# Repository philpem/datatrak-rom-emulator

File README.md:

EPROM Emulator for Datatrak Locator
===================================

This is a plug-in card which replaces the Datatrak "B7415" plug-in ROM card
used with the Locator Mk. II. Its purpose is to allow easier development of
alternative firmware for the Datatrak Locator II, and reverse engineering
of the hardware.

It consists of a 256Kx16 SRAM (512KiB) which can be loaded via an FTDI
FT240X USB serial FIFO and a Xilinx XC95144XL CPLD. The CPLD is programmed
using a JTAG cable.

Mod wires
---------
Rev 'A' boards require a 'mod wire' to be fitted between pin 135 of IC2
(the Xilinx CPLD) and either pin 10 of the SRAM or pin 37 of U3 (the
uppermost voltage level translator).

This wire carries D8 (level translated) from the level translator and SRAM
to the CPLD. Failure to install this wire will prevent D8 from being loaded
by the CPLD.

Known limitations
-----------------

  * The SRAM is powered from the target. Disconnecting target power will
    cause the loss of the data in the emulated EPROM.

    * It might be a good idea to break the power supply to the SRAM and
      feed it via two Schottky diodes: one from +3V3 and one from the FTDI's
      3V output.
      This way, the RAM will be maintained as long as either the USB or
      target is powered.

CPLD configuration
------------------
The CPLD must be programmed before the ROM emulator can be used.

  1. Apply 5V power through the DIN41612 target connector.
  2. 5V power is applied to pins A1 and B1 of the connector, while ground
     is applied to pins A16 and B16.
  3. 3.3V DC should be present on the output of voltage regulator IC1, and
     on JTAG connector X3.
  4. Connect a Xilinx Platform Cable USB (if using iMPACT) or Altera USB
     JTAG cable (if using OpenOCD) to JTAG connector X3.
  5. Use Xilinx iMPACT, OpenOCD or similar to program the CPLD.
    - It's probably easiest to use iMPACT.
  6. Disconnect the JTAG cable, 5V power, etc.
  7. Plug the pod into the Locator and load it.

FT240X configuration
--------------------
The FT240X needs to be programmed with FT-PROG.

  * Program CBUS5 to output the 24MHz clock.
    * This is used by the CPLD as a clock for the state machine.

Exfiltration mode
-----------------
This mode allows the target to access a specially-designated port to use as
a return-channel to the emulation control PC. Essentially, this is like a
secondary, lightweight, "printf".

When an access is made in a specially designated range (address lines
A8..A17 match a preset value), the value of address lines A0 through A7 is
latched, then sent to the FT240X as "write data".

This data may be read by the host PC at its convenience.

It would be nice to add an "infiltration mode" to send data from the PC to
the Locator, but "printf" was a higher priority.

Load protocol
-------------

The data in the FTDI buffer consists of Commands and Data. These are the
Commands which the state machine currently recognises:

  * 0b0000\_0000: NOP
    * Does nothing.
    * Used to reset the state machine to a known state.

  * 0b0000\_0001: Reset Memory Address Counter
    * Resets the memory address to zero

  * 0b0001\_Xemm: Set Mode
    * X: don't care
    * e: Exfiltration mode on/off
      * 0: Off
      * 1: On
    * mm: Mode
      * 00: Run
      * 01: Load

  * 0b0010\_nnnn: Write _nnnn_ words
    * nnnn: Number of words to write
    * Followed by _nnnn_ words of ROM data

  * 0b0100\_xxEE: Set Exfiltration Address
    * EE: Top two bits of exfiltration address (b17..b16)
    * Followed by a byte which contains bits 15..8 of the exfiltration
      address
    * Bits 7..0 are the exfiltration data itself

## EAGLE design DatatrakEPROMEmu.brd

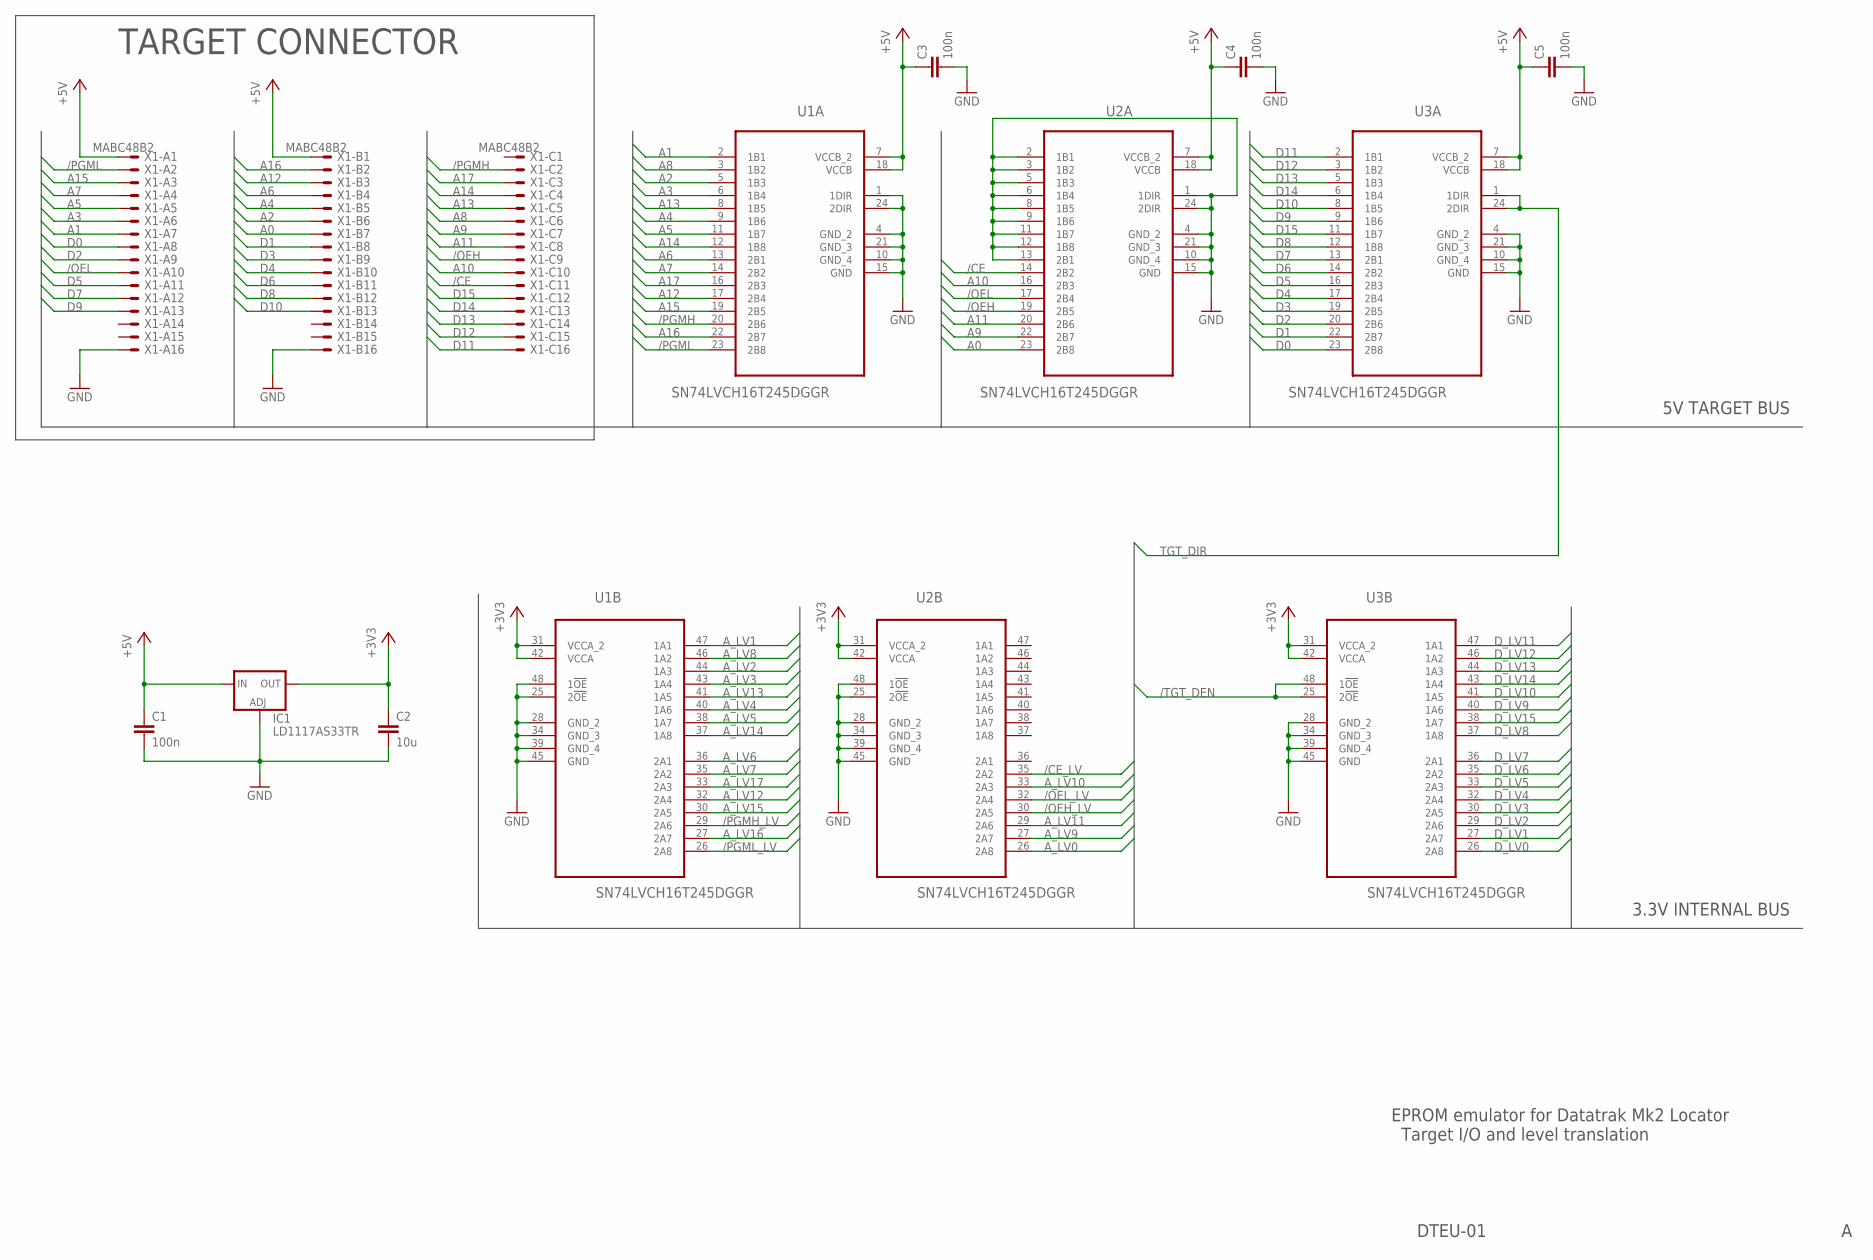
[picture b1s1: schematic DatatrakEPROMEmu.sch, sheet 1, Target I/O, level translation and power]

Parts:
C1, C3, C4, C5: 100n; C0805
C2: 10u; C0805
IC1: LD1117AS33TR; SOT223
U1, U2, U3: SN74LVCH16T245DGGR; SOP50P810X120-48N
X1: MABC48B2

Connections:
+3V3: C2.1, IC1.4 (OUT), U1.31 (VCCA_2), U1.42 (VCCA), U2.31 (VCCA_2), U2.42 (VCCA), U3.31 (VCCA_2), U3.42 (VCCA); also elsewhere on the board
+5V: C1.1, C3.1, C4.1, C5.1, IC1.3 (IN), U1.7 (VCCB_2), U1.18 (VCCB), U2.7 (VCCB_2), U2.18 (VCCB), U3.7 (VCCB_2), U3.18 (VCCB), X1.A1, X1.B1
/CE: U2.14 (2B2), X1.C11
/CE_LV: U2.35 (2A2); also elsewhere on the board
/OEH: U2.19 (2B5), X1.C9
/OEH_LV: U2.30 (2A5); also elsewhere on the board
/OEL: U2.17 (2B4), X1.A10
/OEL_LV: U2.32 (2A4); also elsewhere on the board
/PGMH: U1.20 (2B6), X1.C2
/PGMH_LV: U1.29 (2A6); also elsewhere on the board
/PGML: U1.23 (2B8), X1.A2
/PGML_LV: U1.26 (2A8); also elsewhere on the board
/TGT_DEN: U3.25 (2!OE), U3.48 (1!OE); also elsewhere on the board
A0: U2.23 (2B8), X1.B7
A1: U1.2 (1B1), X1.A7
A2: U1.5 (1B3), X1.B6
A3: U1.6 (1B4), X1.A6
A4: U1.9 (1B6), X1.B5
A5: U1.11 (1B7), X1.A5
A6: U1.13 (2B1), X1.B4
A7: U1.14 (2B2), X1.A4
A8: U1.3 (1B2), X1.C6
A9: U2.22 (2B7), X1.C7
A10: U2.16 (2B3), X1.C10
A11: U2.20 (2B6), X1.C8
A12: U1.17 (2B4), X1.B3
A13: U1.8 (1B5), X1.C5
A14: U1.12 (1B8), X1.C4
A15: U1.19 (2B5), X1.A3
A16: U1.22 (2B7), X1.B2
A17: U1.16 (2B3), X1.C3
A_LV0: U2.26 (2A8); also elsewhere on the board
A_LV1: U1.47 (1A1); also elsewhere on the board
A_LV2: U1.44 (1A3); also elsewhere on the board
A_LV3: U1.43 (1A4); also elsewhere on the board
A_LV4: U1.40 (1A6); also elsewhere on the board
A_LV5: U1.38 (1A7); also elsewhere on the board
A_LV6: U1.36 (2A1); also elsewhere on the board
A_LV7: U1.35 (2A2); also elsewhere on the board
A_LV8: U1.46 (1A2); also elsewhere on the board
A_LV9: U2.27 (2A7); also elsewhere on the board
A_LV10: U2.33 (2A3); also elsewhere on the board
A_LV11: U2.29 (2A6); also elsewhere on the board
A_LV12: U1.32 (2A4); also elsewhere on the board
A_LV13: U1.41 (1A5); also elsewhere on the board
A_LV14: U1.37 (1A8); also elsewhere on the board
A_LV15: U1.30 (2A5); also elsewhere on the board
A_LV16: U1.27 (2A7); also elsewhere on the board
A_LV17: U1.33 (2A3); also elsewhere on the board
D0: U3.23 (2B8), X1.A8
D1: U3.22 (2B7), X1.B8
D2: U3.20 (2B6), X1.A9
D3: U3.19 (2B5), X1.B9
D4: U3.17 (2B4), X1.B10
D5: U3.16 (2B3), X1.A11
D6: U3.14 (2B2), X1.B11
D7: U3.13 (2B1), X1.A12
D8: U3.12 (1B8), X1.B12
D9: U3.9 (1B6), X1.A13
D10: U3.8 (1B5), X1.B13
D11: U3.2 (1B1), X1.C16
D12: U3.3 (1B2), X1.C15
D13: U3.5 (1B3), X1.C14
D14: U3.6 (1B4), X1.C13
D15: U3.11 (1B7), X1.C12
D_LV0: U3.26 (2A8); also elsewhere on the board
D_LV1: U3.27 (2A7); also elsewhere on the board
D_LV2: U3.29 (2A6); also elsewhere on the board
D_LV3: U3.30 (2A5); also elsewhere on the board
D_LV4: U3.32 (2A4); also elsewhere on the board
D_LV5: U3.33 (2A3); also elsewhere on the board
D_LV6: U3.35 (2A2); also elsewhere on the board
D_LV7: U3.36 (2A1); also elsewhere on the board
D_LV8: U3.37 (1A8); also elsewhere on the board
D_LV9: U3.40 (1A6); also elsewhere on the board
D_LV10: U3.41 (1A5); also elsewhere on the board
D_LV11: U3.47 (1A1); also elsewhere on the board
D_LV12: U3.46 (1A2); also elsewhere on the board
D_LV13: U3.44 (1A3); also elsewhere on the board
D_LV14: U3.43 (1A4); also elsewhere on the board
D_LV15: U3.38 (1A7); also elsewhere on the board
GND: C1.2, C2.2, C3.2, C4.2, C5.2, IC1.1 (ADJ), U1.1 (1DIR), U1.4 (GND_2), U1.10 (GND_4), U1.15 (GND), U1.21 (GND_3), U1.24 (2DIR), U1.25 (2!OE), U1.28 (GND_2), U1.34 (GND_3), U1.39 (GND_4), U1.45 (GND), U1.48 (1!OE), U2.1 (1DIR), U2.2 (1B1), U2.3 (1B2), U2.4 (GND_2), U2.5 (1B3), U2.6 (1B4), U2.8 (1B5), U2.9 (1B6), U2.10 (GND_4), U2.11 (1B7), U2.12 (1B8), U2.13 (2B1), U2.15 (GND), U2.21 (GND_3), U2.24 (2DIR), U2.25 (2!OE), U2.28 (GND_2), U2.34 (GND_3), U2.39 (GND_4), U2.45 (GND), U2.48 (1!OE), U3.4 (GND_2), U3.10 (GND_4), U3.15 (GND), U3.21 (GND_3), U3.28 (GND_2), U3.34 (GND_3), U3.39 (GND_4), U3.45 (GND), X1.A16, X1.B16; also elsewhere on the board
TGT_DIR: U3.1 (1DIR), U3.24 (2DIR); also elsewhere on the board

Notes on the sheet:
TARGET CONNECTOR
5V TARGET BUS
3.3V INTERNAL BUS
DTEU-01
EPROM emulator for Datatrak Mk2 Locator Target I/O and level translation

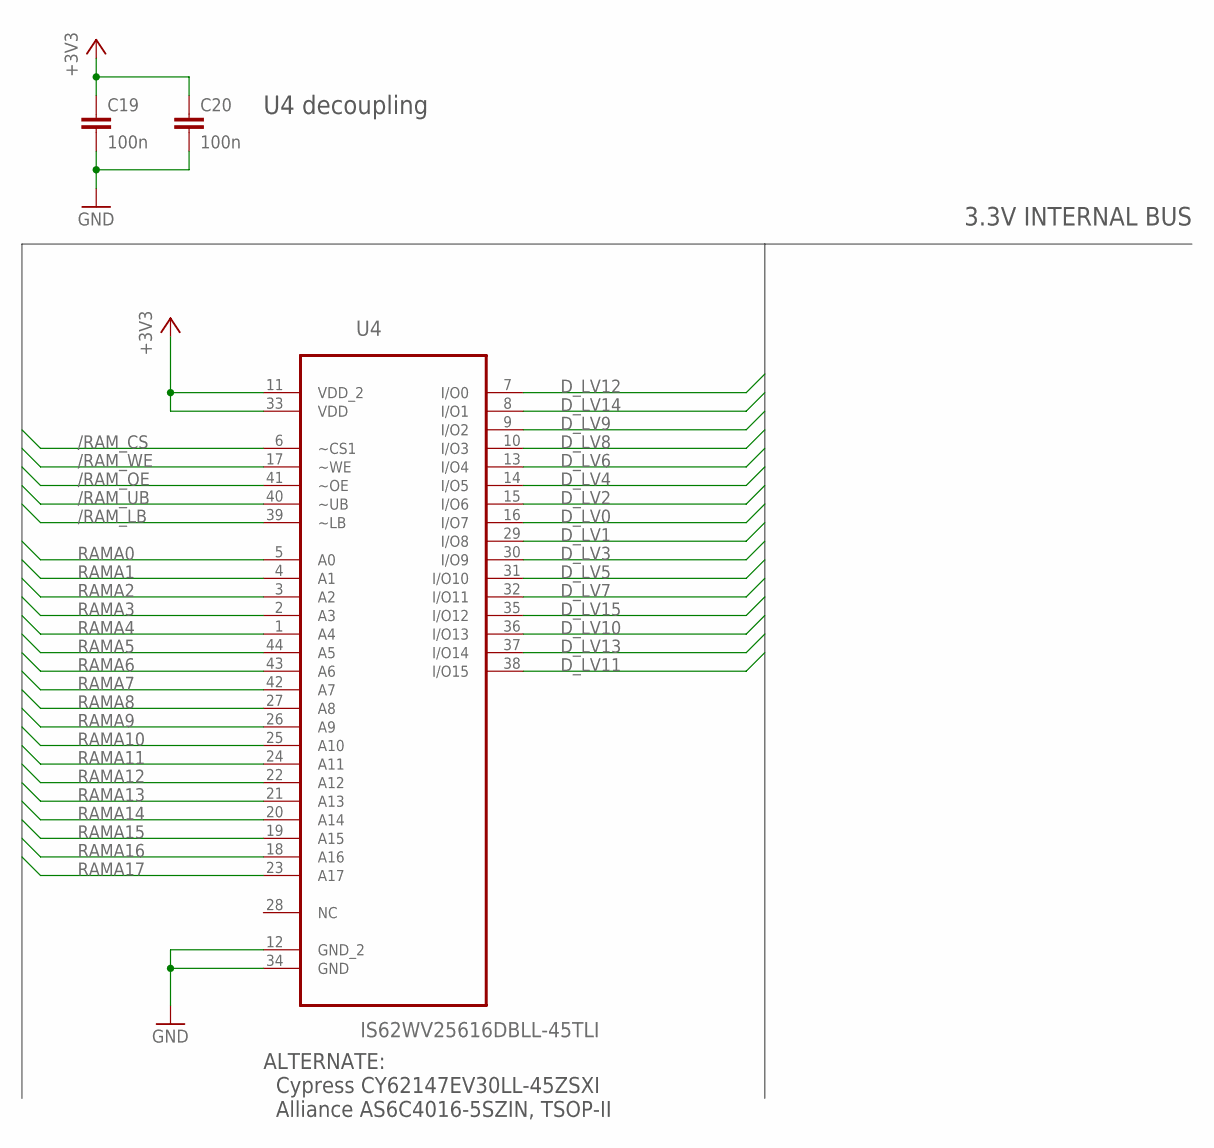
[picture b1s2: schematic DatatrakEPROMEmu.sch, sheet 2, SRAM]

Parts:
C19, C20: 100n; C0805
U4: IS62WV25616DBLL-45TLI; SOP80P1176X120-44N

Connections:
+3V3: C19.1, C20.1, U4.11 (VDD_2), U4.33 (VDD); also elsewhere on the board
/RAM_CS: U4.6 (~CS1); also elsewhere on the board
/RAM_LB: U4.39 (~LB); also elsewhere on the board
/RAM_OE: U4.41 (~OE); also elsewhere on the board
/RAM_UB: U4.40 (~UB); also elsewhere on the board
/RAM_WE: U4.17 (~WE); also elsewhere on the board
D_LV0: U4.16 (I/O7); also elsewhere on the board
D_LV1: U4.29 (I/O8); also elsewhere on the board
D_LV2: U4.15 (I/O6); also elsewhere on the board
D_LV3: U4.30 (I/O9); also elsewhere on the board
D_LV4: U4.14 (I/O5); also elsewhere on the board
D_LV5: U4.31 (I/O10); also elsewhere on the board
D_LV6: U4.13 (I/O4); also elsewhere on the board
D_LV7: U4.32 (I/O11); also elsewhere on the board
D_LV8: U4.10 (I/O3); also elsewhere on the board
D_LV9: U4.9 (I/O2); also elsewhere on the board
D_LV10: U4.36 (I/O13); also elsewhere on the board
D_LV11: U4.38 (I/O15); also elsewhere on the board
D_LV12: U4.7 (I/O0); also elsewhere on the board
D_LV13: U4.37 (I/O14); also elsewhere on the board
D_LV14: U4.8 (I/O1); also elsewhere on the board
D_LV15: U4.35 (I/O12); also elsewhere on the board
GND: C19.2, C20.2, U4.12 (GND_2), U4.34 (GND); also elsewhere on the board
RAMA0: U4.5 (A0); also elsewhere on the board
RAMA1: U4.4 (A1); also elsewhere on the board
RAMA2: U4.3 (A2); also elsewhere on the board
RAMA3: U4.2 (A3); also elsewhere on the board
RAMA4: U4.1 (A4); also elsewhere on the board
RAMA5: U4.44 (A5); also elsewhere on the board
RAMA6: U4.43 (A6); also elsewhere on the board
RAMA7: U4.42 (A7); also elsewhere on the board
RAMA8: U4.27 (A8); also elsewhere on the board
RAMA9: U4.26 (A9); also elsewhere on the board
RAMA10: U4.25 (A10); also elsewhere on the board
RAMA11: U4.24 (A11); also elsewhere on the board
RAMA12: U4.22 (A12); also elsewhere on the board
RAMA13: U4.21 (A13); also elsewhere on the board
RAMA14: U4.20 (A14); also elsewhere on the board
RAMA15: U4.19 (A15); also elsewhere on the board
RAMA16: U4.18 (A16); also elsewhere on the board
RAMA17: U4.23 (A17); also elsewhere on the board

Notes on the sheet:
3.3V INTERNAL BUS
ALTERNATE: Cypress CY62147EV30LL-45ZSXI Alliance AS6C4016-5SZIN, TSOP-II
U4 decoupling

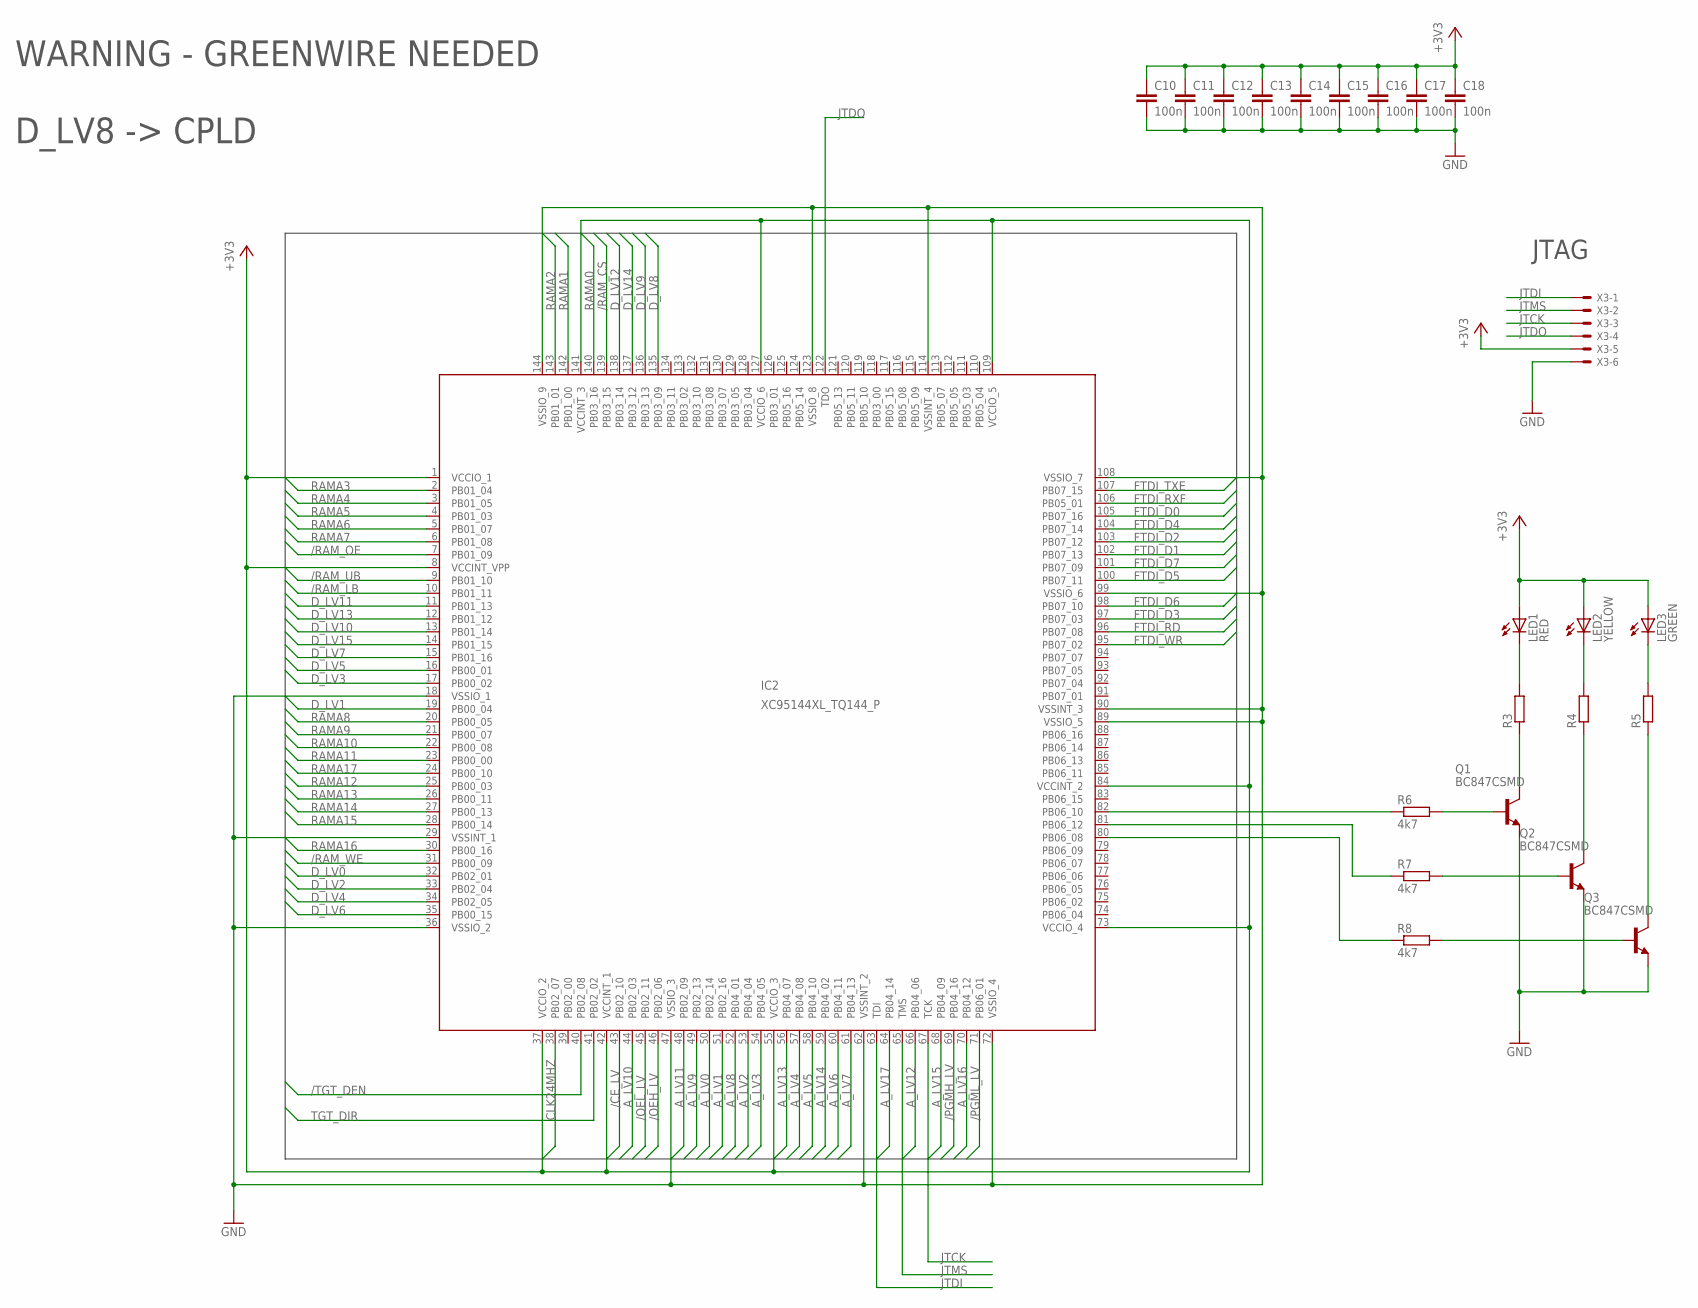
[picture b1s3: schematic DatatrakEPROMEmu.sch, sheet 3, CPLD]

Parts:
C10, C11, C12, C13, C14, C15, C16, C17, C18: 100n; C0805
IC2: XC95144XL_TQ144_P; TQ144
LED1: RED; SML0805
LED2: YELLOW; SML0805
LED3: GREEN; SML0805
Q1, Q2, Q3: BC847CSMD; SOT23
R3, R4, R5: R-EU_R0805; R0805
R6, R7, R8: 4k7; R0805
X3: 22-23-2061

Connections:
+3V3: C10.1, C11.1, C12.1, C13.1, C14.1, C15.1, C16.1, C17.1, C18.1, IC2.1 (VCCIO_1), IC2.8 (VCCINT_VPP), IC2.37 (VCCIO_2), IC2.42 (VCCINT_1), IC2.55 (VCCIO_3), IC2.73 (VCCIO_4), IC2.84 (VCCINT_2), IC2.109 (VCCIO_5), IC2.127 (VCCIO_6), IC2.141 (VCCINT_3), LED1.A, LED2.A, LED3.A, X3.5; also elsewhere on the board
/CE_LV: IC2.43 (PB02_10); also elsewhere on the board
/OEH_LV: IC2.46 (PB02_06); also elsewhere on the board
/OEL_LV: IC2.45 (PB02_11); also elsewhere on the board
/PGMH_LV: IC2.69 (PB04_16); also elsewhere on the board
/PGML_LV: IC2.71 (PB06_01); also elsewhere on the board
/RAM_CS: IC2.139 (PB03_15); also elsewhere on the board
/RAM_LB: IC2.10 (PB01_11); also elsewhere on the board
/RAM_OE: IC2.7 (PB01_09); also elsewhere on the board
/RAM_UB: IC2.9 (PB01_10); also elsewhere on the board
/RAM_WE: IC2.31 (PB00_09); also elsewhere on the board
/TGT_DEN: IC2.40 (PB02_08); also elsewhere on the board
A_LV0: IC2.50 (PB02_14); also elsewhere on the board
A_LV1: IC2.51 (PB02_16); also elsewhere on the board
A_LV2: IC2.53 (PB04_04); also elsewhere on the board
A_LV3: IC2.54 (PB04_05); also elsewhere on the board
A_LV4: IC2.57 (PB04_08); also elsewhere on the board
A_LV5: IC2.58 (PB04_10); also elsewhere on the board
A_LV6: IC2.60 (PB04_11); also elsewhere on the board
A_LV7: IC2.61 (PB04_13); also elsewhere on the board
A_LV8: IC2.52 (PB04_01); also elsewhere on the board
A_LV9: IC2.49 (PB02_13); also elsewhere on the board
A_LV10: IC2.44 (PB02_03); also elsewhere on the board
A_LV11: IC2.48 (PB02_09); also elsewhere on the board
A_LV12: IC2.66 (PB04_06); also elsewhere on the board
A_LV13: IC2.56 (PB04_07); also elsewhere on the board
A_LV14: IC2.59 (PB04_02); also elsewhere on the board
A_LV15: IC2.68 (PB04_09); also elsewhere on the board
A_LV16: IC2.70 (PB04_12); also elsewhere on the board
A_LV17: IC2.64 (PB04_14); also elsewhere on the board
CLK24MHZ: IC2.38 (PB02_07); also elsewhere on the board
D_LV0: IC2.32 (PB02_01); also elsewhere on the board
D_LV1: IC2.19 (PB00_04); also elsewhere on the board
D_LV2: IC2.33 (PB02_04); also elsewhere on the board
D_LV3: IC2.17 (PB00_02); also elsewhere on the board
D_LV4: IC2.34 (PB02_05); also elsewhere on the board
D_LV5: IC2.16 (PB00_01); also elsewhere on the board
D_LV6: IC2.35 (PB00_15); also elsewhere on the board
D_LV7: IC2.15 (PB01_16); also elsewhere on the board
D_LV8: IC2.135 (PB03_09); also elsewhere on the board
D_LV9: IC2.136 (PB03_13); also elsewhere on the board
D_LV10: IC2.13 (PB01_14); also elsewhere on the board
D_LV11: IC2.11 (PB01_13); also elsewhere on the board
D_LV12: IC2.138 (PB03_14); also elsewhere on the board
D_LV13: IC2.12 (PB01_12); also elsewhere on the board
D_LV14: IC2.137 (PB03_12); also elsewhere on the board
D_LV15: IC2.14 (PB01_15); also elsewhere on the board
FTDI_D0: IC2.105 (PB07_16); also elsewhere on the board
FTDI_D1: IC2.102 (PB07_13); also elsewhere on the board
FTDI_D2: IC2.103 (PB07_12); also elsewhere on the board
FTDI_D3: IC2.97 (PB07_03); also elsewhere on the board
FTDI_D4: IC2.104 (PB07_14); also elsewhere on the board
FTDI_D5: IC2.100 (PB07_11); also elsewhere on the board
FTDI_D6: IC2.98 (PB07_10); also elsewhere on the board
FTDI_D7: IC2.101 (PB07_09); also elsewhere on the board
FTDI_RD: IC2.96 (PB07_08); also elsewhere on the board
FTDI_RXF: IC2.106 (PB05_01); also elsewhere on the board
FTDI_TXE: IC2.107 (PB07_15); also elsewhere on the board
FTDI_WR: IC2.95 (PB07_02); also elsewhere on the board
GND: C10.2, C11.2, C12.2, C13.2, C14.2, C15.2, C16.2, C17.2, C18.2, IC2.18 (VSSIO_1), IC2.29 (VSSINT_1), IC2.36 (VSSIO_2), IC2.47 (VSSIO_3), IC2.62 (VSSINT_2), IC2.72 (VSSIO_4), IC2.89 (VSSIO_5), IC2.90 (VSSINT_3), IC2.99 (VSSIO_6), IC2.108 (VSSIO_7), IC2.114 (VSSINT_4), IC2.123 (VSSIO_8), IC2.144 (VSSIO_9), Q1.2 (E), Q2.2 (E), Q3.2 (E), X3.6; also elsewhere on the board
JTCK: IC2.67 (TCK), X3.3
JTDI: IC2.63 (TDI), X3.1
JTDO: IC2.122 (TDO), X3.4
JTMS: IC2.65 (TMS), X3.2
unnamed: Q1.3 (C), R3.1
unnamed: Q2.3 (C), R4.1
unnamed: Q3.3 (C), R5.1
unnamed: LED1.C, R3.2
unnamed: LED2.C, R4.2
unnamed: LED3.C, R5.2
unnamed: IC2.82 (PB06_10), R6.1
unnamed: IC2.81 (PB06_12), R7.1
unnamed: IC2.80 (PB06_08), R8.1
unnamed: Q1.1 (B), R6.2
unnamed: Q2.1 (B), R7.2
unnamed: Q3.1 (B), R8.2
RAMA0: IC2.140 (PB03_16); also elsewhere on the board
RAMA1: IC2.142 (PB01_00); also elsewhere on the board
RAMA2: IC2.143 (PB01_01); also elsewhere on the board
RAMA3: IC2.2 (PB01_04); also elsewhere on the board
RAMA4: IC2.3 (PB01_05); also elsewhere on the board
RAMA5: IC2.4 (PB01_03); also elsewhere on the board
RAMA6: IC2.5 (PB01_07); also elsewhere on the board
RAMA7: IC2.6 (PB01_08); also elsewhere on the board
RAMA8: IC2.20 (PB00_05); also elsewhere on the board
RAMA9: IC2.21 (PB00_07); also elsewhere on the board
RAMA10: IC2.22 (PB00_08); also elsewhere on the board
RAMA11: IC2.23 (PB00_00); also elsewhere on the board
RAMA12: IC2.25 (PB00_03); also elsewhere on the board
RAMA13: IC2.26 (PB00_11); also elsewhere on the board
RAMA14: IC2.27 (PB00_13); also elsewhere on the board
RAMA15: IC2.28 (PB00_14); also elsewhere on the board
RAMA16: IC2.30 (PB00_16); also elsewhere on the board
RAMA17: IC2.24 (PB00_10); also elsewhere on the board
TGT_DIR: IC2.41 (PB02_02); also elsewhere on the board

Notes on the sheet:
JTAG
WARNING - GREENWIRE NEEDED D_LV8 -> CPLD

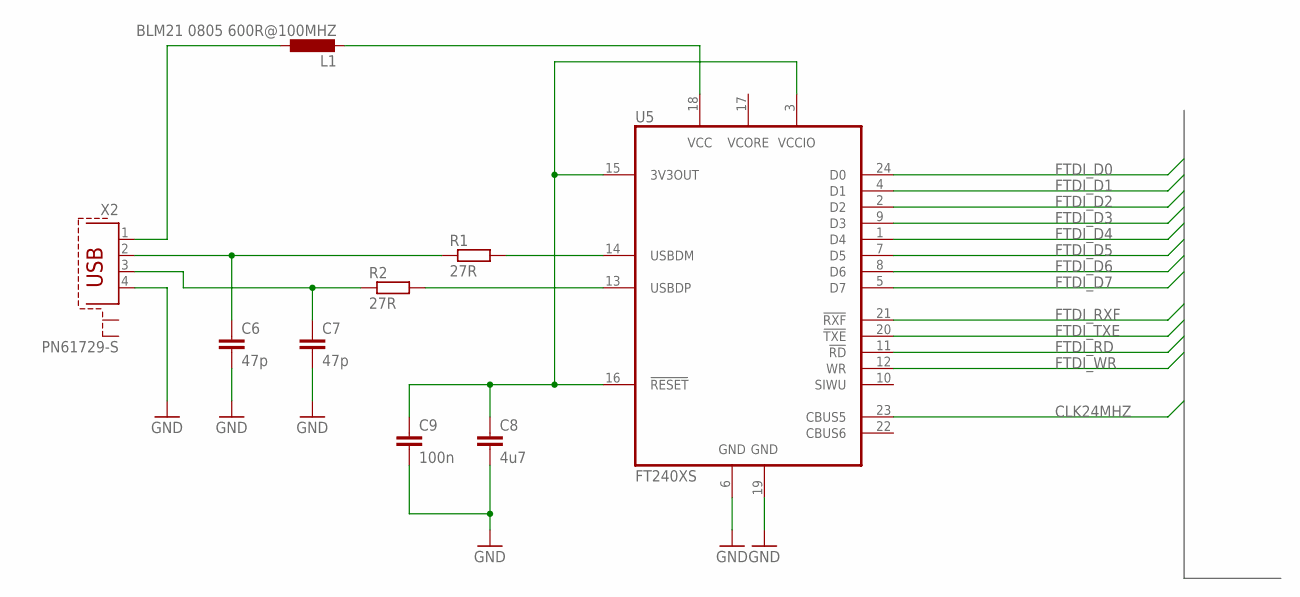
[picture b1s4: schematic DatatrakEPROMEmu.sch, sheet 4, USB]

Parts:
C6, C7: 47p; C0805
C8: 4u7; C0805
C9: 100n; C0805
L1: BLM21 0805 600R@100MHZ; L2012C
R1, R2: 27R; R0805
U5: FT240XS; SSOP24
X2: PN61729-S

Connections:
CLK24MHZ: U5.23 (CBUS5); also elsewhere on the board
FTDI_D0: U5.24 (D0); also elsewhere on the board
FTDI_D1: U5.4 (D1); also elsewhere on the board
FTDI_D2: U5.2 (D2); also elsewhere on the board
FTDI_D3: U5.9 (D3); also elsewhere on the board
FTDI_D4: U5.1 (D4); also elsewhere on the board
FTDI_D5: U5.7 (D5); also elsewhere on the board
FTDI_D6: U5.8 (D6); also elsewhere on the board
FTDI_D7: U5.5 (D7); also elsewhere on the board
FTDI_RD: U5.11 (!RD!); also elsewhere on the board
FTDI_RXF: U5.21 (!RXF!); also elsewhere on the board
FTDI_TXE: U5.20 (!TXE!); also elsewhere on the board
FTDI_WR: U5.12 (WR); also elsewhere on the board
GND: C6.2, C7.2, C8.2, C9.2, U5.6 (GND), U5.19 (GND), X2.4; also elsewhere on the board
unnamed: L1.2, U5.18 (VCC)
unnamed: L1.1, X2.1
unnamed: R1.2, U5.14 (USBDM)
unnamed: R2.2, U5.13 (USBDP)
unnamed: C6.1, R1.1, X2.2
unnamed: C7.1, R2.1, X2.3
unnamed: C8.1, C9.1, U5.3 (VCCIO), U5.15 (3V3OUT), U5.16 (!RESET!)

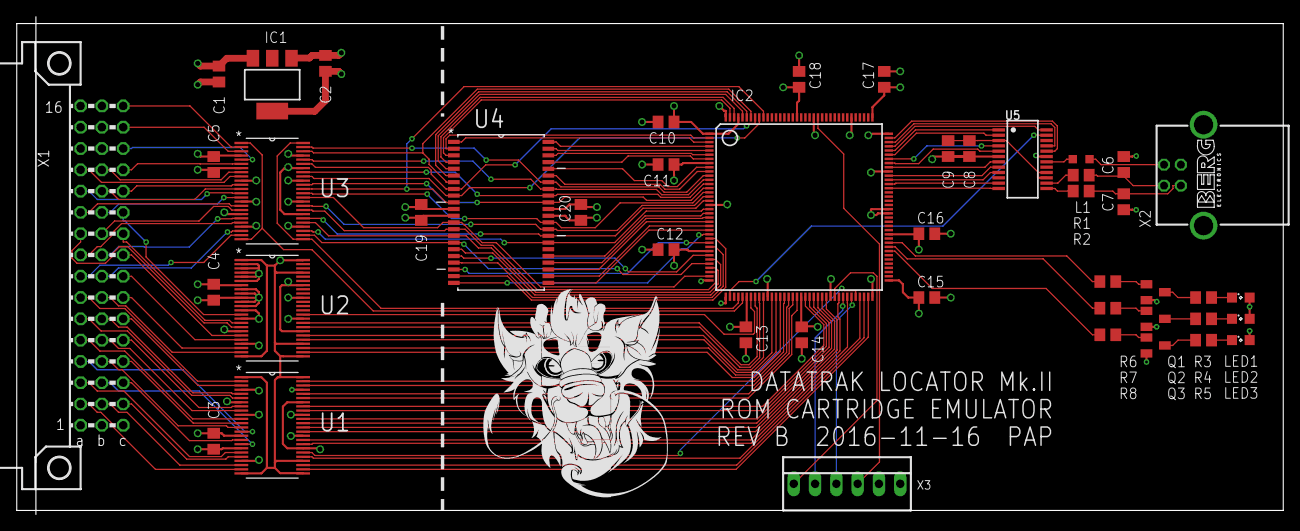
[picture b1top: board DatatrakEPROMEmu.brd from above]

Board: 4 copper layers, 151.1 x 59.4 mm, 46 parts (0 on the bottom side), 142 nets.

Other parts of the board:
U$1: CHAOSLOGO

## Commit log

2016-11-07 initial import
2016-11-12 first routable layout
2016-11-14 add status LEDs
2016-11-14 fully routed
2016-11-14 added good-luck pangon to the silkscreen, this had better work
2016-11-14 fix a few missing routes and ERC errors
2016-11-14 remove right-side marker line
2016-11-14 slight tweaks to silkscreen - move U4 marker line, move IC2 text
2016-11-15 add net labels, remove TODOs
2016-11-16 Tag PCBs sent to OSHPark for manufacture
2016-11-16 add missing D_LV8 net between CPLD and SRAM/translator
    OSHPark PCBs had a missing net -- D_LV8 -- the 8th data bit from the level
    translator to the CPLD. These boards will need a greenwire.
2016-11-16 Route missing D_LV8 net, bump to Rev B
2016-11-16 CPLD: Add logic to set exfiltration mode base address
2016-11-16 Add TODO - original Datatrak ROM board had two separate ROMs, do we need split hi/lo data enables?
2016-11-16 update ISE project
2016-11-16 added README
2016-12-13 Fix to work on final hardware
    * Add testbench and ISIM waveform config
    * Add two hardware test modules (data checkerboard and address loopback)
    Logic changes:
    * Add LEDs - red LED is FTDI activity, yellow is Load mode, green can be
    controlled by the PC.
    * Add FSM command 0x55 and 0xAA to toggle green LED from PC. Intended for
2022-05-22 convert from hgignore to gitignore
2022-07-13 Update gitignore, remove hgignore
2022-07-13 cpld: Initialise mode, exfil-enable and status LED in default state
2022-07-13 cpld: Bugfix: burst writes sometimes cause FSM false command execution
    Burst writes (writes of longer than 1 word) occasionally caused invalid commands to be executed.
    This often manifested as LED state changes / mode changes. (this is more obvious if the LEDs are reconfigured to show `exfiltration_enabled`, `mode[1]` and `mode[0]`).
    Add an extra delay to account for the slight delay while the FT240X makes RXF inactive after the last byte is read.
2022-07-13 cpld: Improve LED output
    * Add activity blink extend timer (LED holds on for 255 clocks on FTDI activity)
    * Change LED behaviour
    * Red: Exfil enabled, blinks on activity
    * Amber: Status LED, XORed with MODE bit 1. (MODE bit 1 is unused, so this should always show the status LED state)
    * Green: Off for LOAD mode, On for RUN mode
2022-07-13 cpld: Fix minor lint issues highlighted by Verilator
2022-07-13 cpld: Renumber states
2022-07-15 add Downloader sources
